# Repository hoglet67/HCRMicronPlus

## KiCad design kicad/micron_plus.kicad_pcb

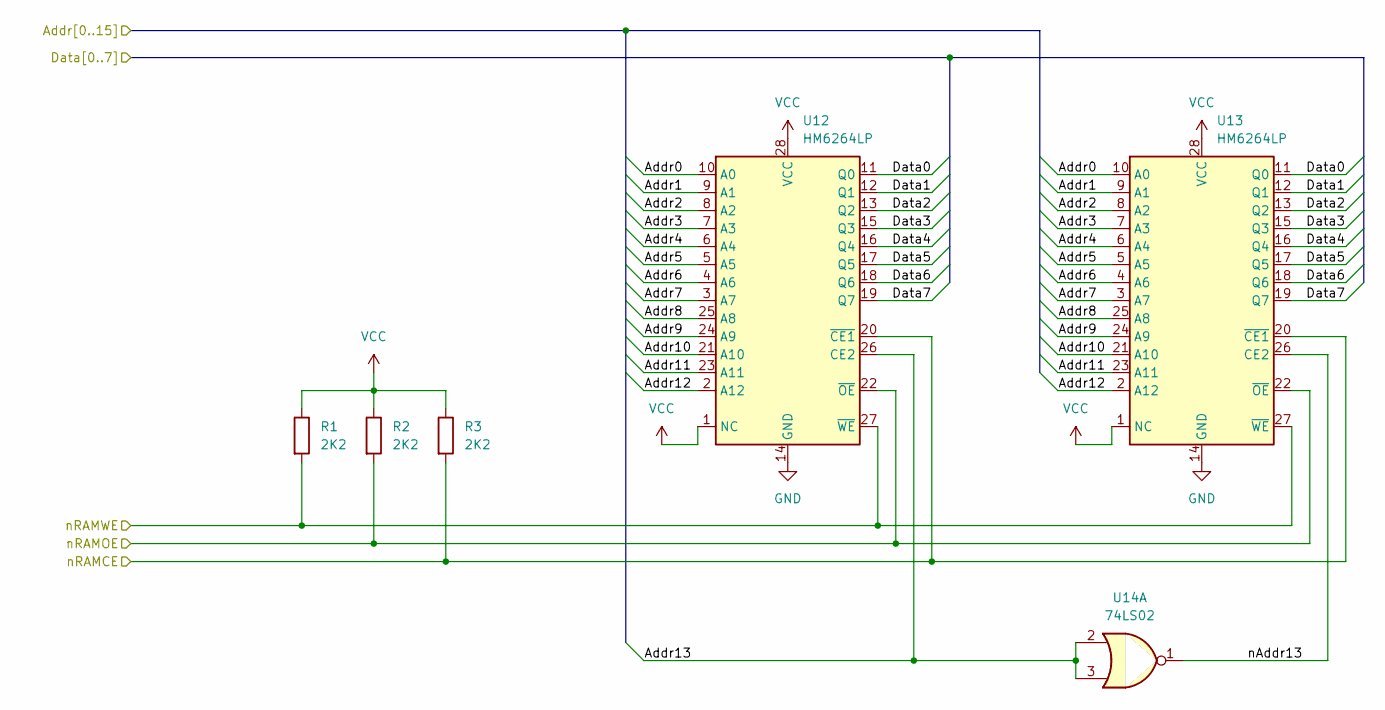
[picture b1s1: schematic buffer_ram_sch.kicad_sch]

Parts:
R1, R2, R3: 2K2; R_Axial_DIN0207_L6.3mm_D2.0mm_P10.16mm_Horizontal
U12, U13: HM6264LP; DIP-28_W15.24mm_Socket
U14: 74LS02; DIP-14_W7.62mm_Socket

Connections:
/1MHz Bus and PIA Interface/Addr0: U12.10 (A0), U13.10 (A0); also elsewhere on the board
/1MHz Bus and PIA Interface/Addr1: U12.9 (A1), U13.9 (A1); also elsewhere on the board
/1MHz Bus and PIA Interface/Addr2: U12.8 (A2), U13.8 (A2); also elsewhere on the board
/1MHz Bus and PIA Interface/Addr3: U12.7 (A3), U13.7 (A3); also elsewhere on the board
/1MHz Bus and PIA Interface/Addr4: U12.6 (A4), U13.6 (A4); also elsewhere on the board
/1MHz Bus and PIA Interface/Addr5: U12.5 (A5), U13.5 (A5); also elsewhere on the board
/1MHz Bus and PIA Interface/Addr6: U12.4 (A6), U13.4 (A6); also elsewhere on the board
/1MHz Bus and PIA Interface/Addr7: U12.3 (A7), U13.3 (A7); also elsewhere on the board
/1MHz Bus and PIA Interface/Addr8: U12.25 (A8), U13.25 (A8); also elsewhere on the board
/1MHz Bus and PIA Interface/Addr9: U12.24 (A9), U13.24 (A9); also elsewhere on the board
/1MHz Bus and PIA Interface/Addr10: U12.21 (A10), U13.21 (A10); also elsewhere on the board
/1MHz Bus and PIA Interface/Addr11: U12.23 (A11), U13.23 (A11); also elsewhere on the board
/1MHz Bus and PIA Interface/Addr12: U12.2 (A12), U13.2 (A12); also elsewhere on the board
/1MHz Bus and PIA Interface/Addr13: U12.26 (CE2), U14.2, U14.3; also elsewhere on the board
/1MHz Bus and PIA Interface/Data0: U12.11 (Q0), U13.11 (Q0); also elsewhere on the board
/1MHz Bus and PIA Interface/Data1: U12.12 (Q1), U13.12 (Q1); also elsewhere on the board
/1MHz Bus and PIA Interface/Data2: U12.13 (Q2), U13.13 (Q2); also elsewhere on the board
/1MHz Bus and PIA Interface/Data3: U12.15 (Q3), U13.15 (Q3); also elsewhere on the board
/1MHz Bus and PIA Interface/Data4: U12.16 (Q4), U13.16 (Q4); also elsewhere on the board
/1MHz Bus and PIA Interface/Data5: U12.17 (Q5), U13.17 (Q5); also elsewhere on the board
/1MHz Bus and PIA Interface/Data6: U12.18 (Q6), U13.18 (Q6); also elsewhere on the board
/1MHz Bus and PIA Interface/Data7: U12.19 (Q7), U13.19 (Q7); also elsewhere on the board
/Buffer RAM/nAddr13: U13.26 (CE2), U14.1
/Control Latches/nRAMCE: R3.2, U12.20 (~CE1), U13.20 (~CE1); also elsewhere on the board
/Control Latches/nRAMOE: R2.2, U12.22 (~OE), U13.22 (~OE); also elsewhere on the board
/Control Latches/nRAMWE: R1.2, U12.27 (~WE), U13.27 (~WE); also elsewhere on the board
GND: U12.14 (GND), U13.14 (GND); also elsewhere on the board
VCC: R1.1, R2.1, R3.1, U12.1 (NC), U12.28 (VCC), U13.1 (NC), U13.28 (VCC); also elsewhere on the board

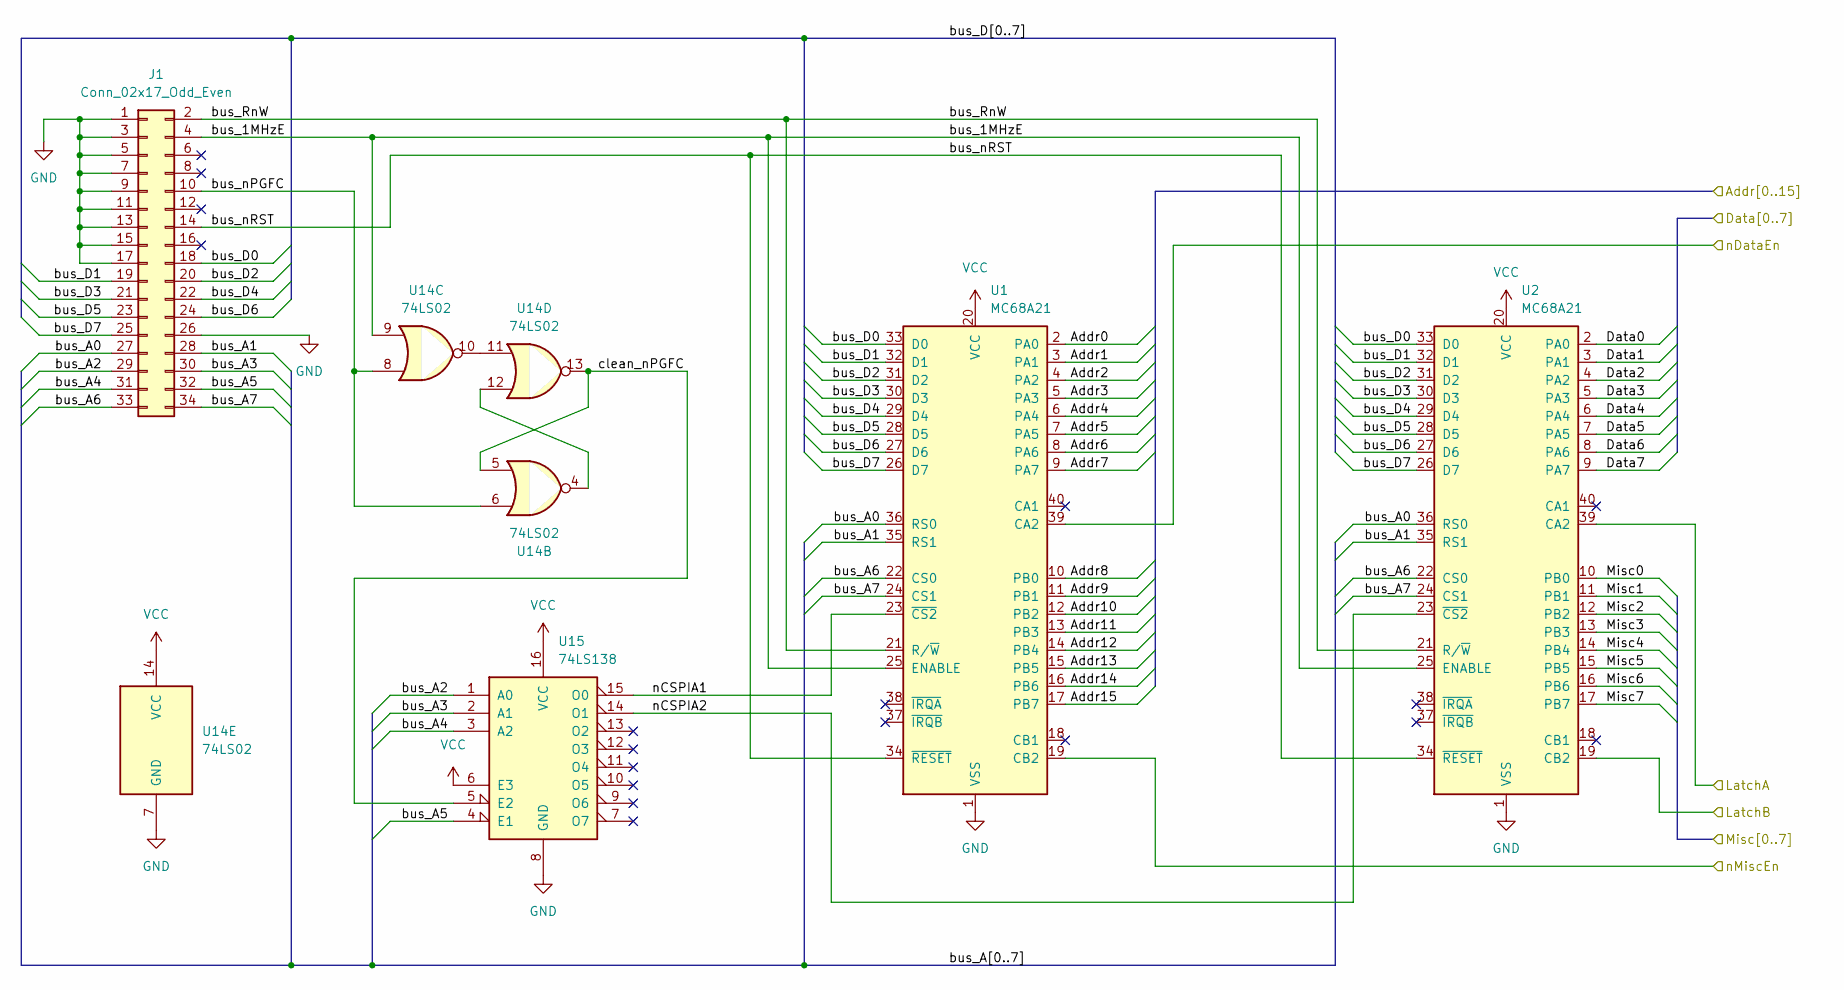
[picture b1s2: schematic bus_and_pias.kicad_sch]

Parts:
J1: Conn_02x17_Odd_Even; IDC-Header_2x17_P2.54mm_Vertical
U1, U2: MC68A21; DIP-40_W15.24mm_Socket
U14: 74LS02; DIP-14_W7.62mm_Socket
U15: 74LS138; DIP-16_W7.62mm_Socket

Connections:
/1MHz Bus and PIA Interface/Addr0: U1.2 (PA0); also elsewhere on the board
/1MHz Bus and PIA Interface/Addr1: U1.3 (PA1); also elsewhere on the board
/1MHz Bus and PIA Interface/Addr2: U1.4 (PA2); also elsewhere on the board
/1MHz Bus and PIA Interface/Addr3: U1.5 (PA3); also elsewhere on the board
/1MHz Bus and PIA Interface/Addr4: U1.6 (PA4); also elsewhere on the board
/1MHz Bus and PIA Interface/Addr5: U1.7 (PA5); also elsewhere on the board
/1MHz Bus and PIA Interface/Addr6: U1.8 (PA6); also elsewhere on the board
/1MHz Bus and PIA Interface/Addr7: U1.9 (PA7); also elsewhere on the board
/1MHz Bus and PIA Interface/Addr8: U1.10 (PB0); also elsewhere on the board
/1MHz Bus and PIA Interface/Addr9: U1.11 (PB1); also elsewhere on the board
/1MHz Bus and PIA Interface/Addr10: U1.12 (PB2); also elsewhere on the board
/1MHz Bus and PIA Interface/Addr11: U1.13 (PB3); also elsewhere on the board
/1MHz Bus and PIA Interface/Addr12: U1.14 (PB4); also elsewhere on the board
/1MHz Bus and PIA Interface/Addr13: U1.15 (PB5); also elsewhere on the board
/1MHz Bus and PIA Interface/Addr14: U1.16 (PB6); also elsewhere on the board
/1MHz Bus and PIA Interface/Addr15: U1.17 (PB7); also elsewhere on the board
/1MHz Bus and PIA Interface/Data0: U2.2 (PA0); also elsewhere on the board
/1MHz Bus and PIA Interface/Data1: U2.3 (PA1); also elsewhere on the board
/1MHz Bus and PIA Interface/Data2: U2.4 (PA2); also elsewhere on the board
/1MHz Bus and PIA Interface/Data3: U2.5 (PA3); also elsewhere on the board
/1MHz Bus and PIA Interface/Data4: U2.6 (PA4); also elsewhere on the board
/1MHz Bus and PIA Interface/Data5: U2.7 (PA5); also elsewhere on the board
/1MHz Bus and PIA Interface/Data6: U2.8 (PA6); also elsewhere on the board
/1MHz Bus and PIA Interface/Data7: U2.9 (PA7); also elsewhere on the board
/1MHz Bus and PIA Interface/LatchA: U2.39 (CA2); also elsewhere on the board
/1MHz Bus and PIA Interface/LatchB: U2.19 (CB2); also elsewhere on the board
/1MHz Bus and PIA Interface/Misc0: U2.10 (PB0); also elsewhere on the board
/1MHz Bus and PIA Interface/Misc1: U2.11 (PB1); also elsewhere on the board
/1MHz Bus and PIA Interface/Misc2: U2.12 (PB2); also elsewhere on the board
/1MHz Bus and PIA Interface/Misc3: U2.13 (PB3); also elsewhere on the board
/1MHz Bus and PIA Interface/Misc4: U2.14 (PB4); also elsewhere on the board
/1MHz Bus and PIA Interface/Misc5: U2.15 (PB5); also elsewhere on the board
/1MHz Bus and PIA Interface/Misc6: U2.16 (PB6); also elsewhere on the board
/1MHz Bus and PIA Interface/Misc7: U2.17 (PB7); also elsewhere on the board
/1MHz Bus and PIA Interface/bus_1MHzE: J1.4, U1.25 (ENABLE), U2.25 (ENABLE), U14.9
/1MHz Bus and PIA Interface/bus_A0: J1.27, U1.36 (RS0), U2.36 (RS0)
/1MHz Bus and PIA Interface/bus_A1: J1.28, U1.35 (RS1), U2.35 (RS1)
/1MHz Bus and PIA Interface/bus_A2: J1.29, U15.1 (A0)
/1MHz Bus and PIA Interface/bus_A3: J1.30, U15.2 (A1)
/1MHz Bus and PIA Interface/bus_A4: J1.31, U15.3 (A2)
/1MHz Bus and PIA Interface/bus_A5: J1.32, U15.4 (E1)
/1MHz Bus and PIA Interface/bus_A6: J1.33, U1.22 (CS0), U2.22 (CS0)
/1MHz Bus and PIA Interface/bus_A7: J1.34, U1.24 (CS1), U2.24 (CS1)
/1MHz Bus and PIA Interface/bus_D0: J1.18, U1.33 (D0), U2.33 (D0)
/1MHz Bus and PIA Interface/bus_D1: J1.19, U1.32 (D1), U2.32 (D1)
/1MHz Bus and PIA Interface/bus_D2: J1.20, U1.31 (D2), U2.31 (D2)
/1MHz Bus and PIA Interface/bus_D3: J1.21, U1.30 (D3), U2.30 (D3)
/1MHz Bus and PIA Interface/bus_D4: J1.22, U1.29 (D4), U2.29 (D4)
/1MHz Bus and PIA Interface/bus_D5: J1.23, U1.28 (D5), U2.28 (D5)
/1MHz Bus and PIA Interface/bus_D6: J1.24, U1.27 (D6), U2.27 (D6)
/1MHz Bus and PIA Interface/bus_D7: J1.25, U1.26 (D7), U2.26 (D7)
/1MHz Bus and PIA Interface/bus_RnW: J1.2, U1.21 (R/~W), U2.21 (R/~W)
/1MHz Bus and PIA Interface/bus_nPGFC: J1.10, U14.6, U14.8
/1MHz Bus and PIA Interface/bus_nRST: J1.14, U1.34 (~RESET), U2.34 (~RESET)
/1MHz Bus and PIA Interface/clean_nPGFC: U14.5, U14.13, U15.5 (E2)
/1MHz Bus and PIA Interface/nCSPIA1: U1.23 (~CS2), U15.15 (O0)
/1MHz Bus and PIA Interface/nCSPIA2: U2.23 (~CS2), U15.14 (O1)
/1MHz Bus and PIA Interface/nDataEn: U1.39 (CA2); also elsewhere on the board
/1MHz Bus and PIA Interface/nMiscEn: U1.19 (CB2); also elsewhere on the board
GND: J1.1, J1.3, J1.5, J1.7, J1.9, J1.11, J1.13, J1.15, J1.17, J1.26, U1.1 (VSS), U2.1 (VSS), U14.7 (GND), U15.8 (GND); also elsewhere on the board
unnamed: U14.10, U14.11
unnamed: U14.4, U14.12
VCC: U1.20 (VCC), U2.20 (VCC), U14.14 (VCC), U15.6 (E3), U15.16 (VCC); also elsewhere on the board

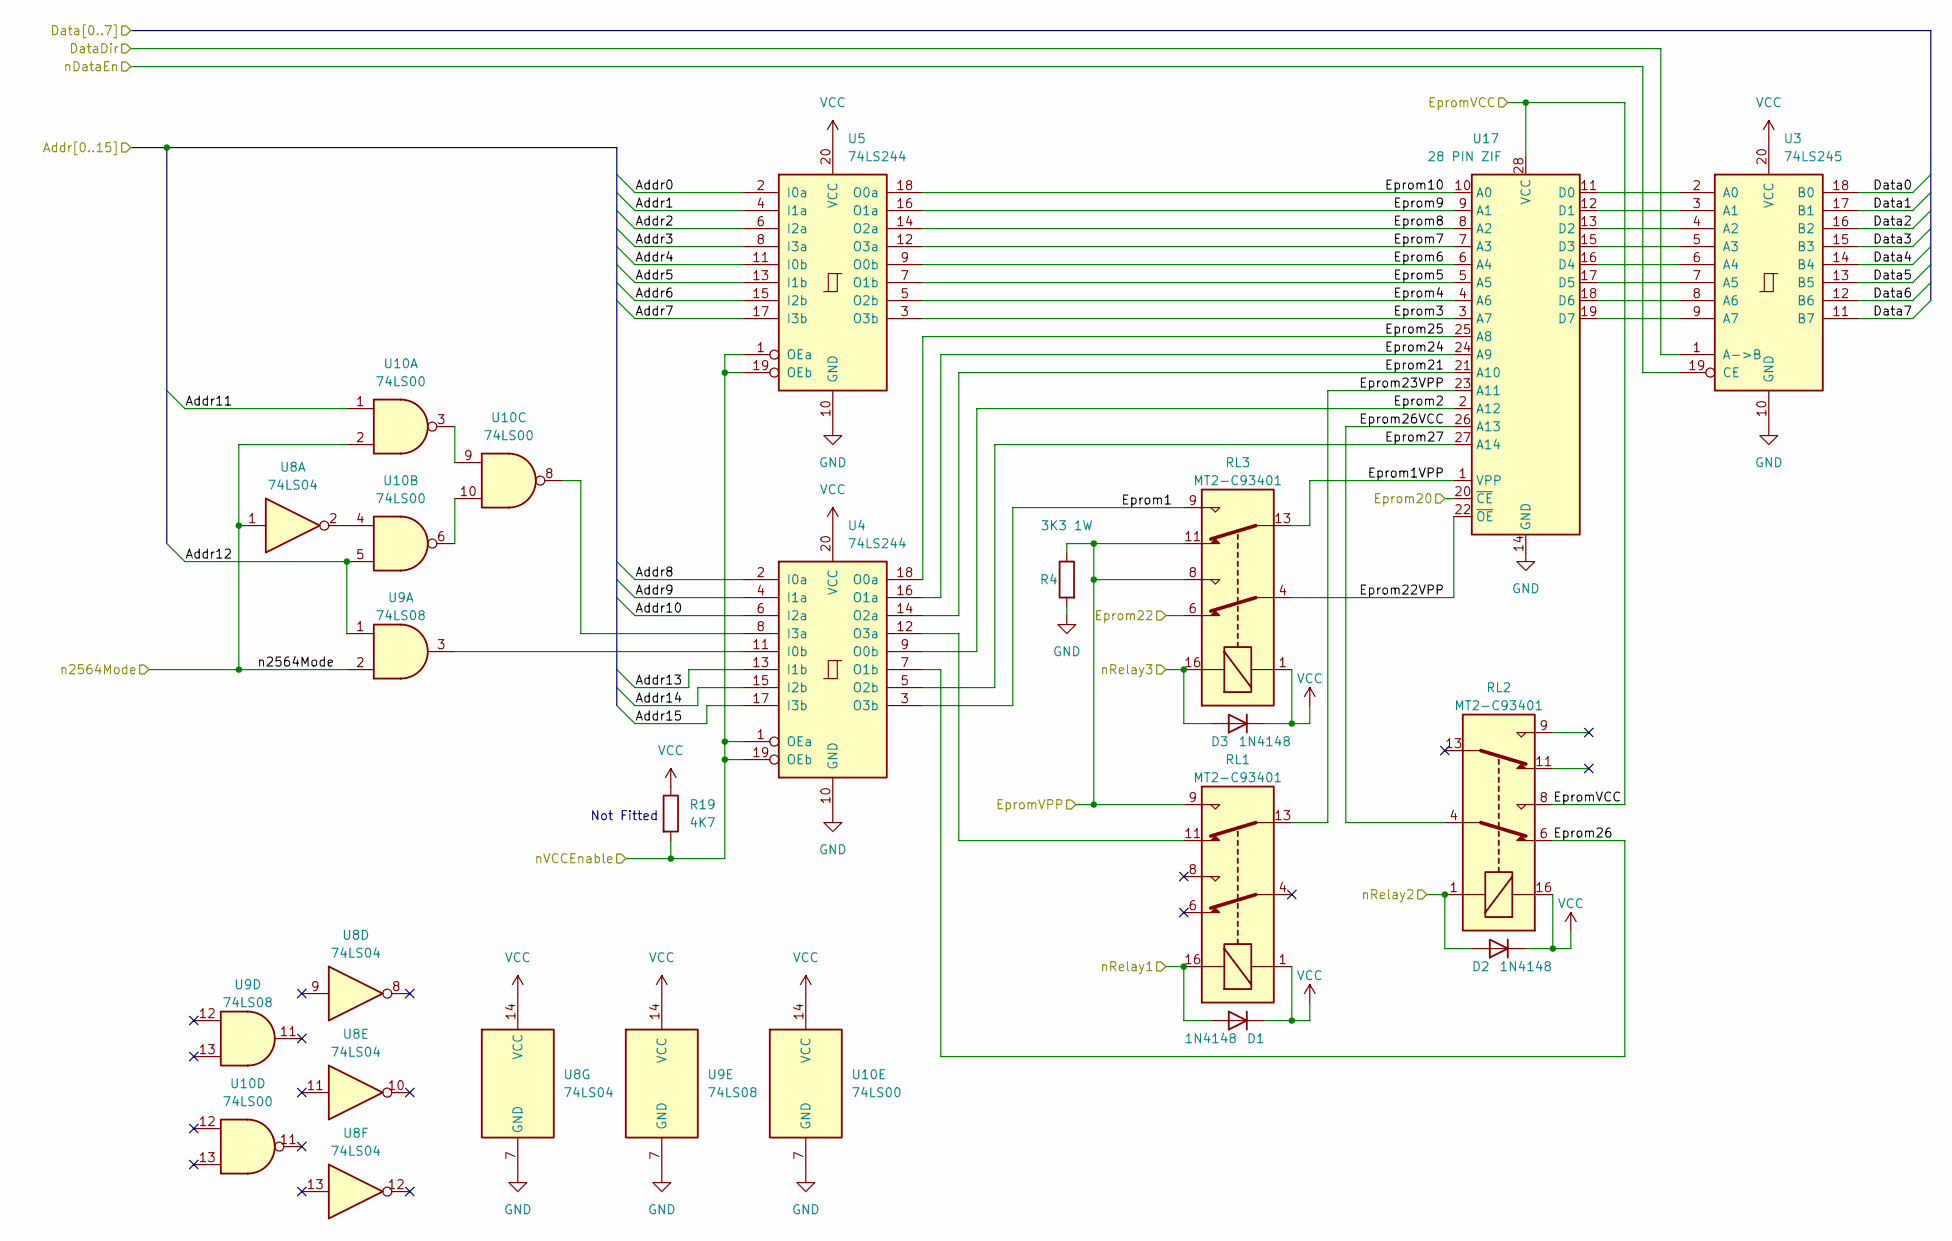
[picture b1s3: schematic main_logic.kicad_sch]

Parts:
D1, D2, D3: 1N4148; D_DO-35_SOD27_P11.43mm_Horizontal
R4: 3K3 1W; R_Axial_DIN0309_L9.0mm_D3.2mm_P12.70mm_Horizontal
R19: 4K7; R_Axial_DIN0207_L6.3mm_D2.0mm_P10.16mm_Horizontal
RL1, RL2, RL3: MT2-C93401; Relay_DPDT_Omron_G5V-2
U3: 74LS245; DIP-20_W7.62mm_Socket_tweaked
U4, U5: 74LS244; DIP-20_W7.62mm_Socket_tweaked
U8: 74LS04; DIP-14_W7.62mm_Socket
U9: 74LS08; DIP-14_W7.62mm_Socket
U10: 74LS00; DIP-14_W7.62mm_Socket
U17: 28 PIN ZIF; DIP_Socket-28_W11.9_W12.7_W15.24_W17.78_W18.5_3M_228-1277-0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

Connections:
/1MHz Bus and PIA Interface/Addr0: U5.2 (I0a); also elsewhere on the board
/1MHz Bus and PIA Interface/Addr1: U5.4 (I1a); also elsewhere on the board
/1MHz Bus and PIA Interface/Addr2: U5.6 (I2a); also elsewhere on the board
/1MHz Bus and PIA Interface/Addr3: U5.8 (I3a); also elsewhere on the board
/1MHz Bus and PIA Interface/Addr4: U5.11 (I0b); also elsewhere on the board
/1MHz Bus and PIA Interface/Addr5: U5.13 (I1b); also elsewhere on the board
/1MHz Bus and PIA Interface/Addr6: U5.15 (I2b); also elsewhere on the board
/1MHz Bus and PIA Interface/Addr7: U5.17 (I3b); also elsewhere on the board
/1MHz Bus and PIA Interface/Addr8: U4.2 (I0a); also elsewhere on the board
/1MHz Bus and PIA Interface/Addr9: U4.4 (I1a); also elsewhere on the board
/1MHz Bus and PIA Interface/Addr10: U4.6 (I2a); also elsewhere on the board
/1MHz Bus and PIA Interface/Addr11: U10.1; also elsewhere on the board
/1MHz Bus and PIA Interface/Addr12: U9.1, U10.5; also elsewhere on the board
/1MHz Bus and PIA Interface/Addr13: U4.13 (I1b); also elsewhere on the board
/1MHz Bus and PIA Interface/Addr14: U4.15 (I2b); also elsewhere on the board
/1MHz Bus and PIA Interface/Addr15: U4.17 (I3b); also elsewhere on the board
/1MHz Bus and PIA Interface/Data0: U3.18 (B0); also elsewhere on the board
/1MHz Bus and PIA Interface/Data1: U3.17 (B1); also elsewhere on the board
/1MHz Bus and PIA Interface/Data2: U3.16 (B2); also elsewhere on the board
/1MHz Bus and PIA Interface/Data3: U3.15 (B3); also elsewhere on the board
/1MHz Bus and PIA Interface/Data4: U3.14 (B4); also elsewhere on the board
/1MHz Bus and PIA Interface/Data5: U3.13 (B5); also elsewhere on the board
/1MHz Bus and PIA Interface/Data6: U3.12 (B6); also elsewhere on the board
/1MHz Bus and PIA Interface/Data7: U3.11 (B7); also elsewhere on the board
/1MHz Bus and PIA Interface/nDataEn: U3.19 (CE); also elsewhere on the board
/Control Latches/DataDir: U3.1 (A->B); also elsewhere on the board
/Control Latches/Eprom20: U17.20 (~CE); also elsewhere on the board
/Control Latches/Eprom22: RL3.6; also elsewhere on the board
/Control Latches/n2564Mode: U8.1, U9.2, U10.2; also elsewhere on the board
/Control Latches/nRelay1: D1.2 (A), RL1.16; also elsewhere on the board
/Control Latches/nRelay2: D2.2 (A), RL2.1; also elsewhere on the board
/Control Latches/nRelay3: D3.2 (A), RL3.16; also elsewhere on the board
/Control Latches/nVCCEnable: R19.2, U4.1 (OEa), U4.19 (OEb), U5.1 (OEa), U5.19 (OEb); also elsewhere on the board
/Main Logic and Eprom Socket/Eprom1: RL3.9, U4.3 (O3b)
/Main Logic and Eprom Socket/Eprom1VPP: RL3.13, U17.1 (VPP)
/Main Logic and Eprom Socket/Eprom2: U4.9 (O0b), U17.2 (A12)
/Main Logic and Eprom Socket/Eprom3: U5.3 (O3b), U17.3 (A7)
/Main Logic and Eprom Socket/Eprom4: U5.5 (O2b), U17.4 (A6)
/Main Logic and Eprom Socket/Eprom5: U5.7 (O1b), U17.5 (A5)
/Main Logic and Eprom Socket/Eprom6: U5.9 (O0b), U17.6 (A4)
/Main Logic and Eprom Socket/Eprom7: U5.12 (O3a), U17.7 (A3)
/Main Logic and Eprom Socket/Eprom8: U5.14 (O2a), U17.8 (A2)
/Main Logic and Eprom Socket/Eprom9: U5.16 (O1a), U17.9 (A1)
/Main Logic and Eprom Socket/Eprom10: U5.18 (O0a), U17.10 (A0)
/Main Logic and Eprom Socket/Eprom21: U4.14 (O2a), U17.21 (A10)
/Main Logic and Eprom Socket/Eprom22VPP: RL3.4, U17.22 (~OE)
/Main Logic and Eprom Socket/Eprom23VPP: RL1.13, U17.23 (A11)
/Main Logic and Eprom Socket/Eprom24: U4.16 (O1a), U17.24 (A9)
/Main Logic and Eprom Socket/Eprom25: U4.18 (O0a), U17.25 (A8)
/Main Logic and Eprom Socket/Eprom26: RL2.6, U4.7 (O1b)
/Main Logic and Eprom Socket/Eprom26VCC: RL2.4, U17.26 (A13)
/Main Logic and Eprom Socket/Eprom27: U4.5 (O2b), U17.27 (A14)
/Main Logic and Eprom Socket/EpromVCC: RL2.8, U17.28 (VCC); also elsewhere on the board
/Main Logic and Eprom Socket/EpromVPP: R4.1, RL1.9, RL3.8, RL3.11; also elsewhere on the board
GND: R4.2, U3.10 (GND), U4.10 (GND), U5.10 (GND), U8.7 (GND), U9.7 (GND), U10.7 (GND), U17.14 (GND); also elsewhere on the board
unnamed: RL1.11, U4.12 (O3a)
unnamed: U4.11 (I0b), U9.3
unnamed: U10.3, U10.9
unnamed: U8.2, U10.4
unnamed: U4.8 (I3a), U10.8
unnamed: U10.6, U10.10
unnamed: U3.2 (A0), U17.11 (D0)
unnamed: U3.3 (A1), U17.12 (D1)
unnamed: U3.4 (A2), U17.13 (D2)
unnamed: U3.5 (A3), U17.15 (D3)
unnamed: U3.6 (A4), U17.16 (D4)
unnamed: U3.7 (A5), U17.17 (D5)
unnamed: U3.8 (A6), U17.18 (D6)
unnamed: U3.9 (A7), U17.19 (D7)
VCC: D1.1 (K), D2.1 (K), D3.1 (K), R19.1, RL1.1, RL2.16, RL3.1, U3.20 (VCC), U4.20 (VCC), U5.20 (VCC), U8.14 (VCC), U9.14 (VCC), U10.14 (VCC); also elsewhere on the board

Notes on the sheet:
Not Fitted

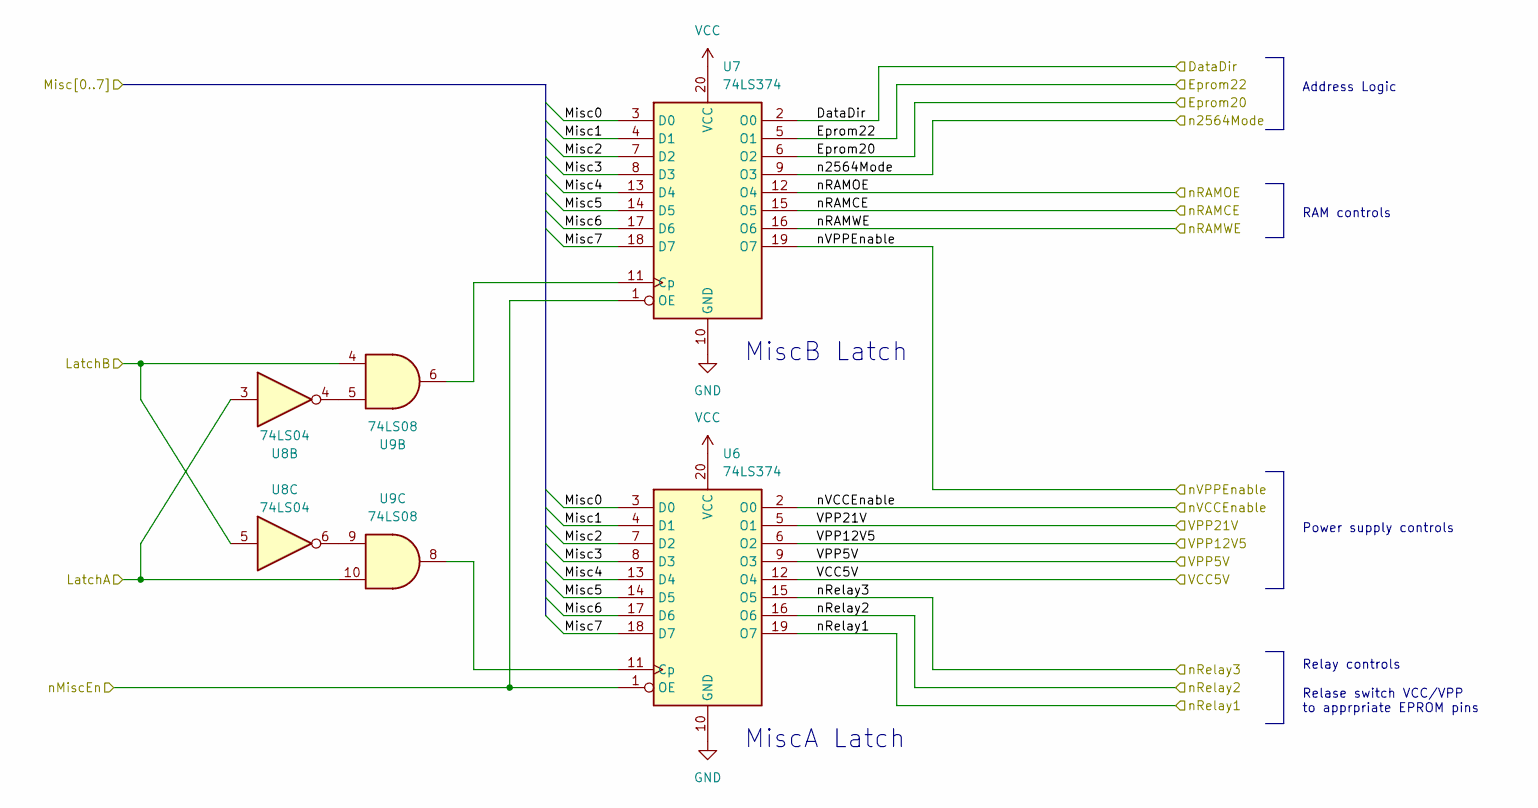
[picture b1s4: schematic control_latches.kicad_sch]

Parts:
U6, U7: 74LS374; DIP-20_W7.62mm_Socket
U8: 74LS04; DIP-14_W7.62mm_Socket
U9: 74LS08; DIP-14_W7.62mm_Socket

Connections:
/1MHz Bus and PIA Interface/LatchA: U8.3, U9.10; also elsewhere on the board
/1MHz Bus and PIA Interface/LatchB: U8.5, U9.4; also elsewhere on the board
/1MHz Bus and PIA Interface/Misc0: U6.3 (D0), U7.3 (D0); also elsewhere on the board
/1MHz Bus and PIA Interface/Misc1: U6.4 (D1), U7.4 (D1); also elsewhere on the board
/1MHz Bus and PIA Interface/Misc2: U6.7 (D2), U7.7 (D2); also elsewhere on the board
/1MHz Bus and PIA Interface/Misc3: U6.8 (D3), U7.8 (D3); also elsewhere on the board
/1MHz Bus and PIA Interface/Misc4: U6.13 (D4), U7.13 (D4); also elsewhere on the board
/1MHz Bus and PIA Interface/Misc5: U6.14 (D5), U7.14 (D5); also elsewhere on the board
/1MHz Bus and PIA Interface/Misc6: U6.17 (D6), U7.17 (D6); also elsewhere on the board
/1MHz Bus and PIA Interface/Misc7: U6.18 (D7), U7.18 (D7); also elsewhere on the board
/1MHz Bus and PIA Interface/nMiscEn: U6.1 (OE), U7.1 (OE); also elsewhere on the board
/Control Latches/DataDir: U7.2 (O0); also elsewhere on the board
/Control Latches/Eprom20: U7.6 (O2); also elsewhere on the board
/Control Latches/Eprom22: U7.5 (O1); also elsewhere on the board
/Control Latches/VCC5V: U6.12 (O4); also elsewhere on the board
/Control Latches/VPP5V: U6.9 (O3); also elsewhere on the board
/Control Latches/VPP12V5: U6.6 (O2); also elsewhere on the board
/Control Latches/VPP21V: U6.5 (O1); also elsewhere on the board
/Control Latches/n2564Mode: U7.9 (O3); also elsewhere on the board
/Control Latches/nRAMCE: U7.15 (O5); also elsewhere on the board
/Control Latches/nRAMOE: U7.12 (O4); also elsewhere on the board
/Control Latches/nRAMWE: U7.16 (O6); also elsewhere on the board
/Control Latches/nRelay1: U6.19 (O7); also elsewhere on the board
/Control Latches/nRelay2: U6.16 (O6); also elsewhere on the board
/Control Latches/nRelay3: U6.15 (O5); also elsewhere on the board
/Control Latches/nVCCEnable: U6.2 (O0); also elsewhere on the board
/Control Latches/nVPPEnable: U7.19 (O7); also elsewhere on the board
GND: U6.10 (GND), U7.10 (GND); also elsewhere on the board
unnamed: U6.11 (Cp), U9.8
unnamed: U7.11 (Cp), U9.6
unnamed: U8.4, U9.5
unnamed: U8.6, U9.9
VCC: U6.20 (VCC), U7.20 (VCC); also elsewhere on the board

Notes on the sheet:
RAM controls
Address Logic
Power supply controls
MiscA Latch
Relay controls Relase switch VCC/VPP to apprpriate EPROM pins
MiscB Latch

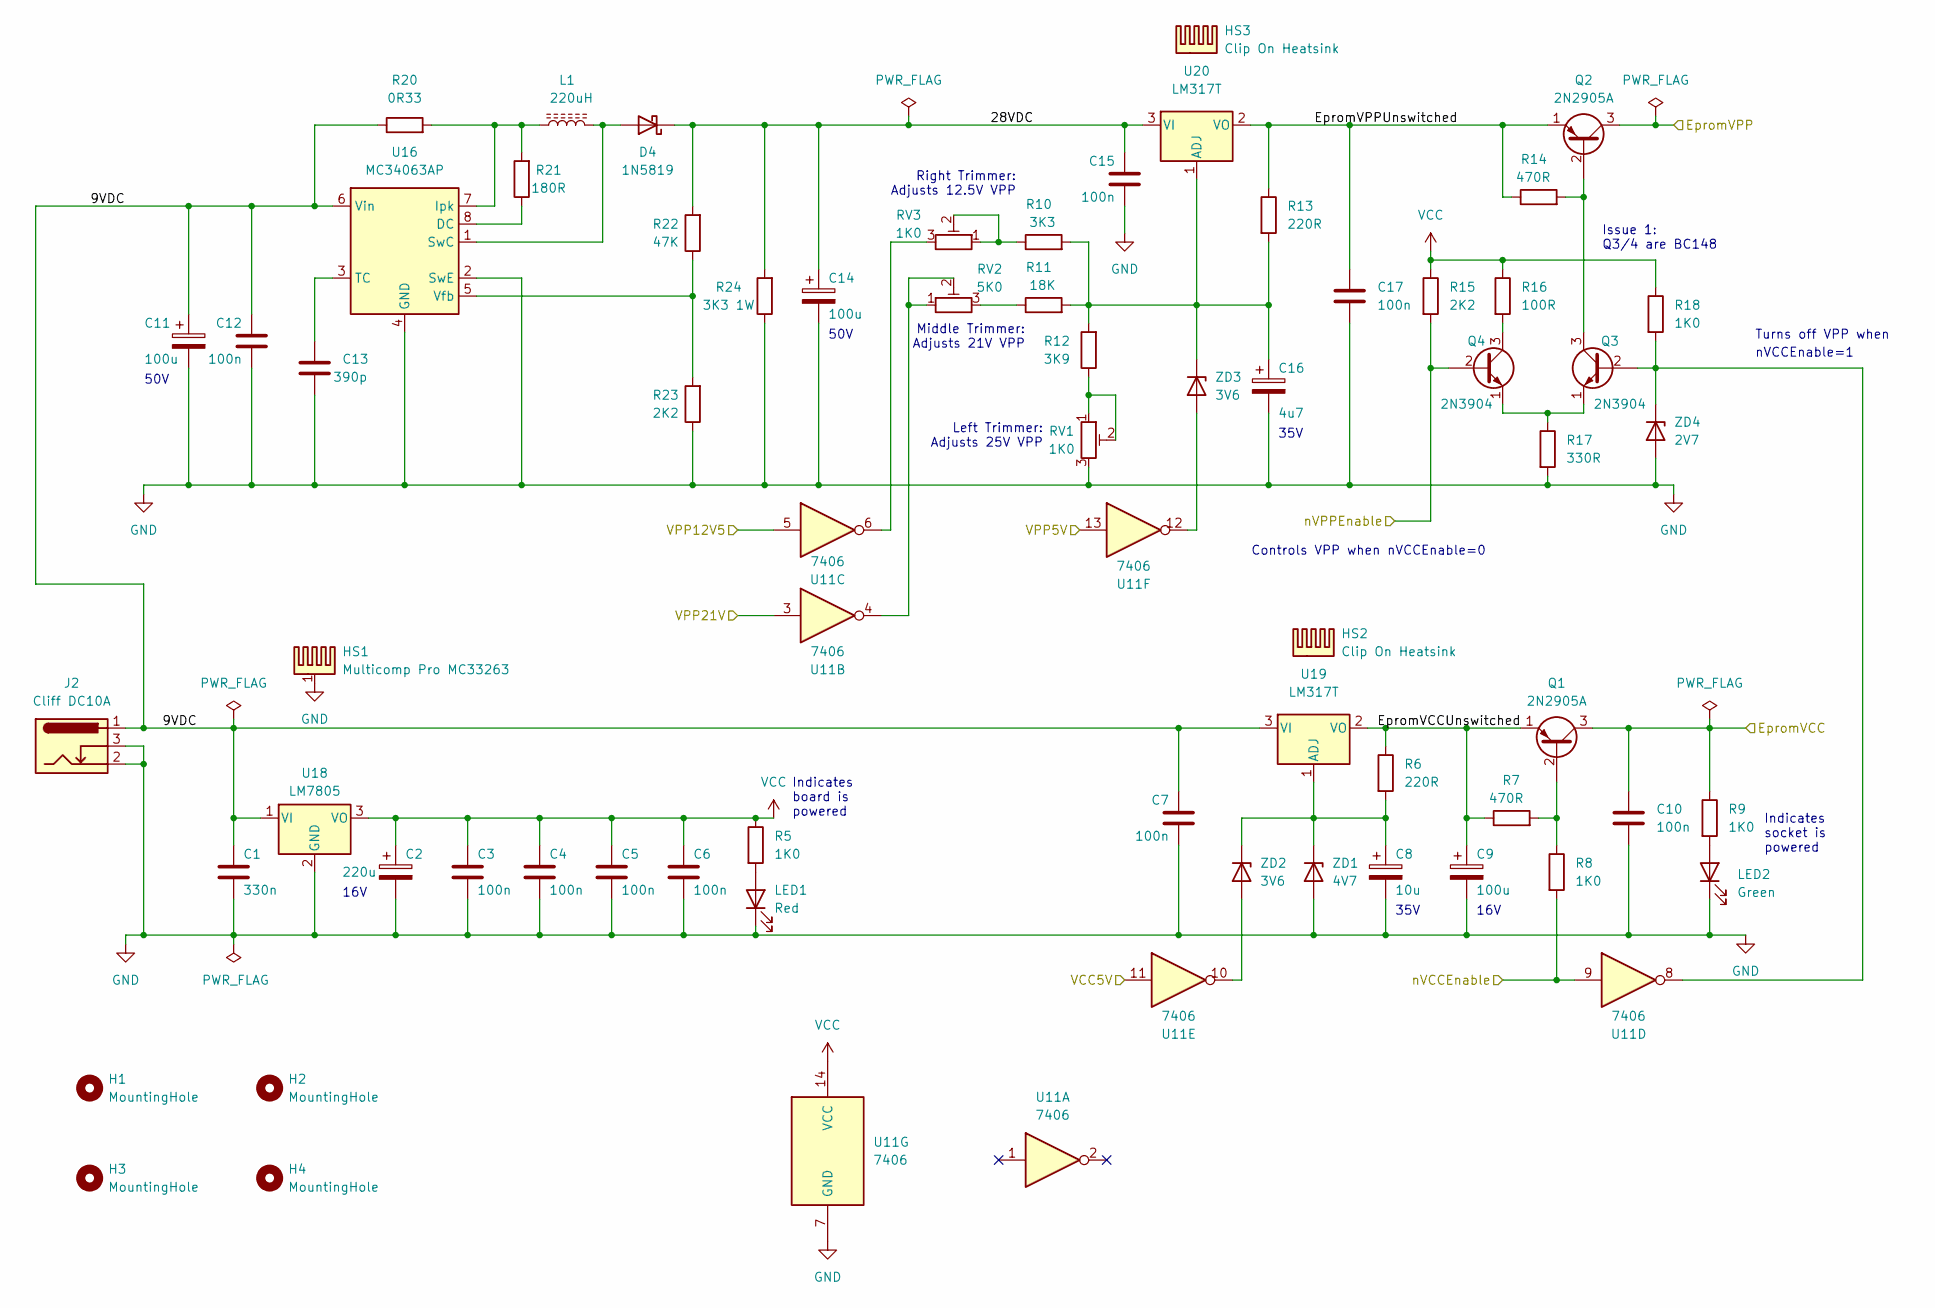
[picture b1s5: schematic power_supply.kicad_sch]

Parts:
C1: 330n; C_Disc_D4.3mm_W1.9mm_P5.00mm
C2: 220u; CP_Radial_D8.0mm_P5.00mm
C3, C4, C5, C6, C7, C10, C12, C15, C17: 100n; C_Disc_D4.3mm_W1.9mm_P5.00mm
C8: 10u; CP_Radial_Tantal_D4.5mm_P5.00mm
C9: 100u; CP_Radial_D6.3mm_P2.50mm
C11, C14: 100u; CP_Radial_D8.0mm_P5.00mm
C13: 390p; C_Disc_D4.3mm_W1.9mm_P5.00mm
C16: 4u7; CP_Radial_Tantal_D4.5mm_P5.00mm
D4: 1N5819; D_DO-41_SOD81_P10.16mm_Horizontal
H1, H2, H3, H4: MountingHole; MountingHole_3.2mm_M3
HS1: Multicomp Pro MC33263; Heatsink_Fischer_SK104-STC-STIC_35x13mm_2xDrill2.5mm
HS2, HS3: Clip On Heatsink; Heatsink_Boyd_PF720
J2: Cliff DC10A; CLIFF_FC68148(DC-10A)
L1: 220uH; L_Radial_D14.2mm_P10.00mm_Kemet
LED1: Red; LED_D3.0mm
LED2: Green; LED_D3.0mm
Q1, Q2: 2N2905A; TO-39-3
Q3, Q4: 2N3904; TO-92_Wide
R5, R9: 1K0; R_Axial_DIN0207_L6.3mm_D2.0mm_P10.16mm_Horizontal
R6, R13: 220R; R_Axial_DIN0207_L6.3mm_D2.0mm_P11.43mm_Horizontal
R7: 470R; R_Axial_DIN0207_L6.3mm_D2.0mm_P11.43mm_Horizontal
R8, R18: 1K0; R_Axial_DIN0207_L6.3mm_D2.0mm_P11.43mm_Horizontal
R10: 3K3; R_Axial_DIN0207_L6.3mm_D2.0mm_P11.43mm_Horizontal
R11: 18K; R_Axial_DIN0207_L6.3mm_D2.0mm_P11.43mm_Horizontal
R12: 3K9; R_Axial_DIN0207_L6.3mm_D2.0mm_P11.43mm_Horizontal
R14: 470R; R_Axial_DIN0207_L6.3mm_D2.0mm_P10.16mm_Horizontal
R15: 2K2; R_Axial_DIN0207_L6.3mm_D2.0mm_P11.43mm_Horizontal
R16: 100R; R_Axial_DIN0207_L6.3mm_D2.0mm_P11.43mm_Horizontal
R17: 330R; R_Axial_DIN0207_L6.3mm_D2.0mm_P11.43mm_Horizontal
R20: 0R33; R_Axial_DIN0207_L6.3mm_D2.5mm_P10.16mm_Horizontal
R21: 180R; R_Axial_DIN0207_L6.3mm_D2.0mm_P10.16mm_Horizontal
R22: 47K; R_Axial_DIN0207_L6.3mm_D2.0mm_P10.16mm_Horizontal
R23: 2K2; R_Axial_DIN0207_L6.3mm_D2.0mm_P10.16mm_Horizontal
R24: 3K3 1W; R_Axial_DIN0309_L9.0mm_D3.2mm_P12.70mm_Horizontal
RV1, RV3: 1K0; Potentiometer_Bourns_3296W_Vertical
RV2: 5K0; Potentiometer_Bourns_3296W_Vertical
U11: 7406; DIP-14_W7.62mm_Socket
U16: MC34063AP; DIP-8_W7.62mm_Socket
U18: LM7805; TO-220-3_Vertical
U19, U20: LM317T; TO-220-3_Vertical
ZD1: 4V7; D_DO-35_SOD27_P11.43mm_Horizontal
ZD2, ZD3: 3V6; D_DO-35_SOD27_P11.43mm_Horizontal
ZD4: 2V7; D_DO-35_SOD27_P11.43mm_Horizontal

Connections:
/Control Latches/VCC5V: U11.11; also elsewhere on the board
/Control Latches/VPP5V: U11.13; also elsewhere on the board
/Control Latches/VPP12V5: U11.5; also elsewhere on the board
/Control Latches/VPP21V: U11.3; also elsewhere on the board
/Control Latches/nVCCEnable: R8.2, U11.9; also elsewhere on the board
/Control Latches/nVPPEnable: Q4.2 (B), R15.2; also elsewhere on the board
/Main Logic and Eprom Socket/EpromVCC: C10.1, Q1.3 (C), R9.1; also elsewhere on the board
/Main Logic and Eprom Socket/EpromVPP: Q2.3 (C); also elsewhere on the board
/Power Supply/9VDC: C1.1, C7.1, C11.1, C12.1, J2.1, R20.1, U16.6 (Vin), U18.1 (VI), U19.3 (VI)
/Power Supply/28VDC: C14.1, C15.1, D4.1 (K), R22.2, R24.2, U20.3 (VI)
/Power Supply/EpromVCCUnswitched: C9.1, Q1.1 (E), R6.1, R7.1, U19.2 (VO)
/Power Supply/EpromVPPUnswitched: C17.1, Q2.1 (E), R13.1, R14.1, U20.2 (VO)
GND: C1.2, C2.2, C3.2, C4.2, C5.2, C6.2, C7.2, C8.2, C9.2, C10.2, C11.2, C12.2, C13.2, C14.2, C15.2, C16.2, C17.2, HS1.1, J2.2, J2.3, LED1.1 (K), LED2.1 (K), R17.2, R23.1, R24.1, RV1.3, U11.7 (GND), U16.2 (SwE), U16.4 (GND), U18.2 (GND), ZD1.2 (A), ZD4.2 (A); also elsewhere on the board
unnamed: C8.1, R6.2, U19.1 (ADJ), ZD1.1 (K), ZD2.1 (K)
unnamed: C13.1, U16.3 (TC)
unnamed: C16.1, R10.2, R11.2, R12.2, R13.2, U20.1 (ADJ), ZD3.1 (K)
unnamed: D4.2 (A), L1.2, U16.1 (SwC)
unnamed: L1.1, R20.2, R21.2, U16.7 (Ipk)
unnamed: LED1.2 (A), R5.2
unnamed: LED2.2 (A), R9.2
unnamed: Q1.2 (B), R7.2, R8.1
unnamed: Q2.2 (B), Q3.3 (C), R14.2
unnamed: Q3.1 (E), Q4.1 (E), R17.1
unnamed: Q3.2 (B), R18.2, U11.8, ZD4.1 (K)
unnamed: Q4.3 (C), R16.2
unnamed: R10.1, RV3.1, RV3.2
unnamed: R11.1, RV2.3
unnamed: R12.1, RV1.1, RV1.2
unnamed: R21.1, U16.8 (DC)
unnamed: R22.1, R23.2, U16.5 (Vfb)
unnamed: RV2.1, RV2.2, U11.4
unnamed: RV3.3, U11.6
unnamed: U11.10, ZD2.2 (A)
unnamed: U11.12, ZD3.2 (A)
VCC: C2.1, C3.1, C4.1, C5.1, C6.1, R5.1, R15.1, R16.1, R18.1, U11.14 (VCC), U18.3 (VO); also elsewhere on the board

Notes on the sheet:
Left Trimmer: Adjusts 25V VPP
16V
50V
Indicates socket is powered
35V
Indicates board is powered
Controls VPP when nVCCEnable=0
Turns off VPP when
Right Trimmer: Adjusts 12.5V VPP
Middle Trimmer: Adjusts 21V VPP
nVCCEnable=1
Issue 1: Q3/4 are BC148
